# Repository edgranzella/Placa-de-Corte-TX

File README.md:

# Plaquetita de Corte TX - Hardware y PCB 🚀

Este repositorio contiene el diseño completo de la placa de circuito impreso (PCB) desarrollado en **KiCad** para el módulo **Plaquetita de Corte TX**. 

Este circuito está diseñado para actuar como un módulo de interrupción, conmutación o protección rápida en las líneas de transmisión (TX) o señales críticas de RF/Comunicaciones.

---

## 📌 Características del Diseño
* **Corte y Conmutación de Señal:** Etapa optimizada para la interrupción limpia de líneas de datos o transmisión sin atenuación excesiva.
* **Protección de Línea:** Incorporación de componentes de protección contra transitorios (ESD/TVS) en los terminales de entrada y salida.
* **Dimensiones Reducidas:** Diseño ultracompacto ideal para ser integrado como módulo secundario (piggyback) o en gabinetes pequeños.

---

## 🛠️ Especificaciones Técnicas de Fabricación
Configuración sugerida basada en las reglas de diseño (DRC) aplicadas en KiCad:

| Parámetro | Configuración Sugerida |
| :--- | :--- |
| **Capas (Layers)** | 2 Capas |
| **Grosor de la Placa** | 1.6 mm / 1.0 mm (si se busca menor perfil) |
| **Acabado Superficial** | HASL (with lead) o ENIG (Recomendado para señales de alta velocidad) |

---

## 👥 Desarrollado por
* **Damian Granzella** - *Ingeniería de Hardware* - [edgranzella](https://github.com)

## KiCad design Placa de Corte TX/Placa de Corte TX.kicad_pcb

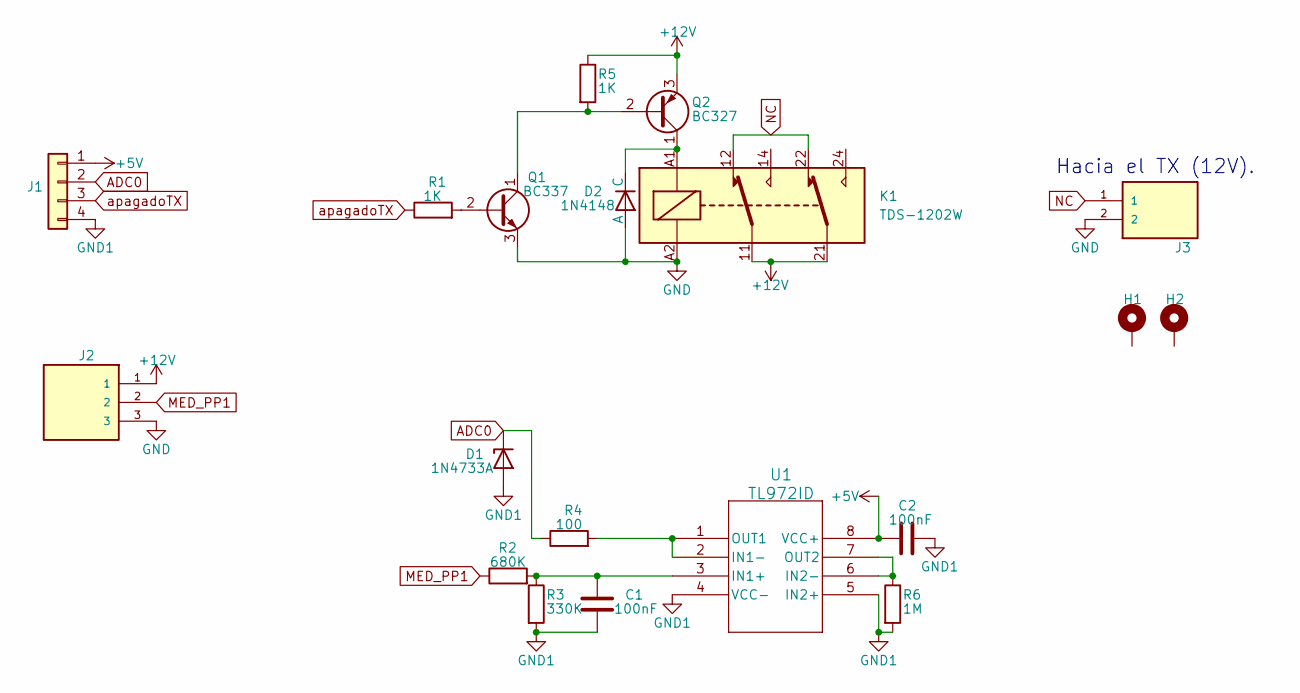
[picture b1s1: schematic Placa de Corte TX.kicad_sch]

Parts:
C1, C2: 100nF; C_Disc_D5.0mm_W2.5mm_P2.50mm
D1: 1N4733A; D_DO-41_SOD81_P10.16mm_Horizontal
D2: 1N4148; D_DO-35_SOD27_P5.08mm_Horizontal
H1, H2: MountingHole_Pad; MountingHole_3.2mm_M3_Pad
J1: Conn_01x04; PinHeader_1x04_P2.54mm_Vertical
J2: TBP01R1-508-03BE; TerminalBlock_Phoenix_MKDS-1,5-2-5.08_1x03_P5.08mm_Horizont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
J3: TBP01R1-508-02BE; TerminalBlock_Phoenix_MKDS-1,5-2-5.08_1x02_P5.08mm_Horizont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
K1: TDS-1202W; Relay_DPDT_Finder_30.22
Q1: BC337; TO-92_HandSolder
Q2: BC327; TO-92_HandSolder
R1, R5: 1K; R_Axial_DIN0207_L6.3mm_D2.5mm_P7.62mm_Horizontal
R2: 680K; R_Axial_DIN0207_L6.3mm_D2.5mm_P7.62mm_Horizontal
R3: 330K; R_Axial_DIN0207_L6.3mm_D2.5mm_P7.62mm_Horizontal
R4: 100; R_Axial_DIN0207_L6.3mm_D2.5mm_P7.62mm_Horizontal
R6: 1M; R_Axial_DIN0207_L6.3mm_D2.5mm_P7.62mm_Horizontal
U1: TL972ID; D8

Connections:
+5V: C2.2, J1.1, U1.8 (VCC+)
+12V: J2.1, K1.11, K1.21, Q2.3 (E), R5.1
ADC0: D1.1 (K), J1.2, R4.1
GND: D2.1 (A), J2.3, J3.2, K1.A2, Q1.3 (E)
GND1: C1.1, C2.1, D1.2 (A), J1.4, R3.2, R6.2, U1.4 (VCC-), U1.5 (IN2+)
MED_PP1: J2.2, R2.1
NC: J3.1, K1.12, K1.22
unnamed: D2.2 (C), K1.A1, Q2.1 (C)
unnamed: Q1.2 (B), R1.2
unnamed: Q1.1 (C), Q2.2 (B), R5.2
unnamed: C1.2, R2.2, R3.1, U1.3 (IN1+)
unnamed: R4.2, U1.1 (OUT1), U1.2 (IN1-)
unnamed: R6.1, U1.6 (IN2-), U1.7 (OUT2)
apagadoTX: J1.3, R1.1

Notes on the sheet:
Hacia el TX (12V).

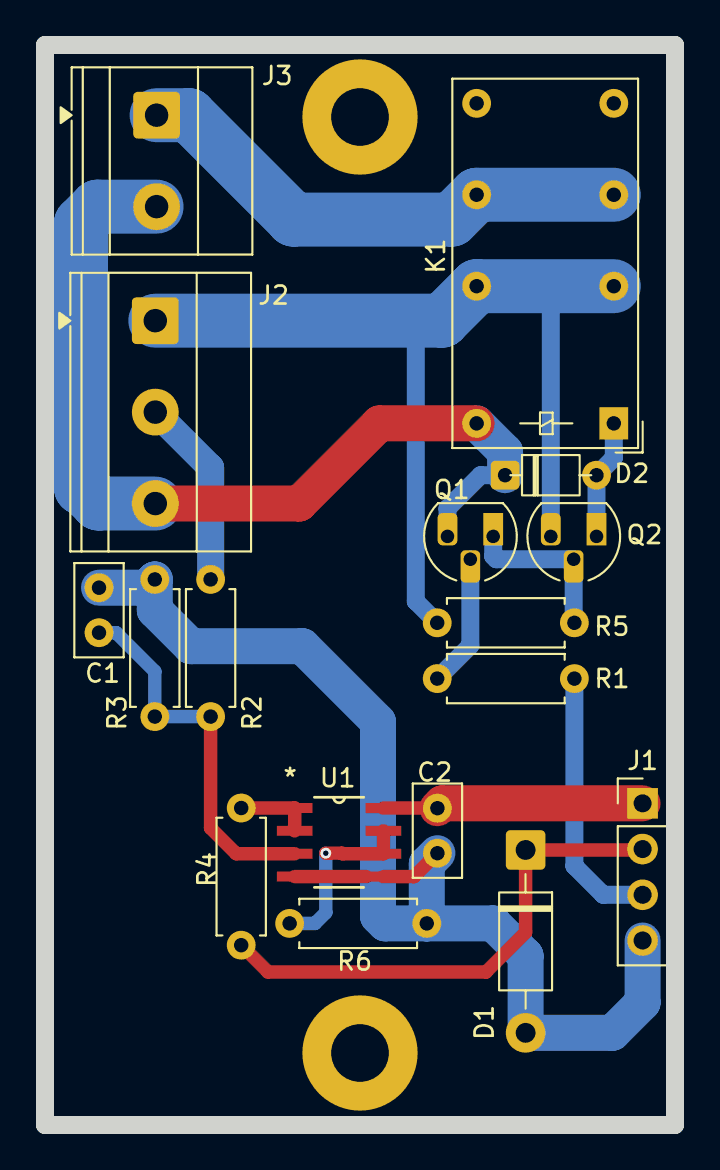
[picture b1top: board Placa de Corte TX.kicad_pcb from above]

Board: 2 copper layers, 35.0 x 60.0 mm, 19 parts (0 on the bottom side), 14 nets.

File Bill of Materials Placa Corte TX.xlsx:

Lista de Materiales Plaquetita de Corte TX
Reference | Qty | Código | Value | Descripción
C1, C2 | 2 | 60020011 | 100nF / 50V | Condensador cerámico de inserción (THT), 100 nF, 50V.
D1 | 1 | 60040119 | 1N4733A | Diodo Zener de inserción (THT), encapsulado DO-41, tensión Zener de 5.1V, poten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
D2 | 1 | 60041001 | 1N4148 | Diodo de conmutación rápida de inserción (THT), encapsulado DO-35, 100V, 300mA
J1 | 1 | 60002025 | Conn_01x04 | Conector macho de inserción (THT), 1 fila de 4 pines, paso estándar de 2.54 mm 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
J2 | 1 | 60000002 | TBP01R1-508-03BE | Bloque de terminales de tornillo para circuito impreso (PCB) de inserción (THT)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
J3 | 1 | 60000001 | TBP01R1-508-02BE | Bloque de terminales de tornillo para circuito impreso (PCB) de inserción (THT)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
K1 | 1 | 60090004 | TDS-1202W | Relé electromecánico de potencia de inserción (THT), bobina de activación de 12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
Q1 | 1 | 60053001 | BC337 | Transistor bipolar NPN de inserción (THT), encapsulado TO-92, 45V, 800mA.
Q2 | 1 | 60053000 | BC327 | Transistor bipolar PNP de inserción (THT), encapsulado TO-92, 45V, 800mA.
R1, R5 | 2 | 60012080 | 1K 1/4W | Resistencia de película de carbón o metal de inserción (THT), potencia de 1/4W 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
R2 | 1 | 60012027 | 680K 1/4W | Resistencia de película de carbón o metal de inserción (THT), potencia de 1/4W 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
R3 | 1 | 60012065 | 330K 1/4W | Resistencia de película de carbón o metal de inserción (THT), potencia de 1/4W 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
R4 | 1 | 60012012 | 100 1/4W | Resistencia de película de carbón o metal de inserción (THT), potencia de 1/4W 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
R6 | 1 | 60012071 | 1M 1/4W | Resistencia de película de carbón o metal de inserción (THT), potencia de 1/4W 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
U1 | 1 | 60069210 | TL972ID | Amplificador operacional doble de bajo ruido y salida Rail-to-Rail, encapsulado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
